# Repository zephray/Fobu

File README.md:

Fobu
====

Fobu is a key fob sized open-source FPGA + ARM handheld device (formerly VerilogBoy Handheld). The intended usages are portable FPGA retro gaming system (FPGA-based implementation, ARM-based emulation, or both) and portable audio (both general format such as mp3, FLAC, etc. via ARM core and retro VGM such as FM, SSG, etc. via FPGA implementation) player. However, the architecture should allow other usages as well.

# Hardware

## Block Diagram

## Photos

The photo of an Fobu r0.2 prototype:

# Software

The following third-party middlewares are used in the project:

 * Amazon FreeRTOS Operating System (MIT)
 * id3v2lib by Lorenzo Ruiz (BSD 2-Clause)
 * minimp3 by lieff (Public Domain)
 * FatFs by ChaN (See source file)
 * tjpgd by ChaN (See source file)

# License

If not otherwise specified, all the materials provided in this repository are licensed under MIT license.

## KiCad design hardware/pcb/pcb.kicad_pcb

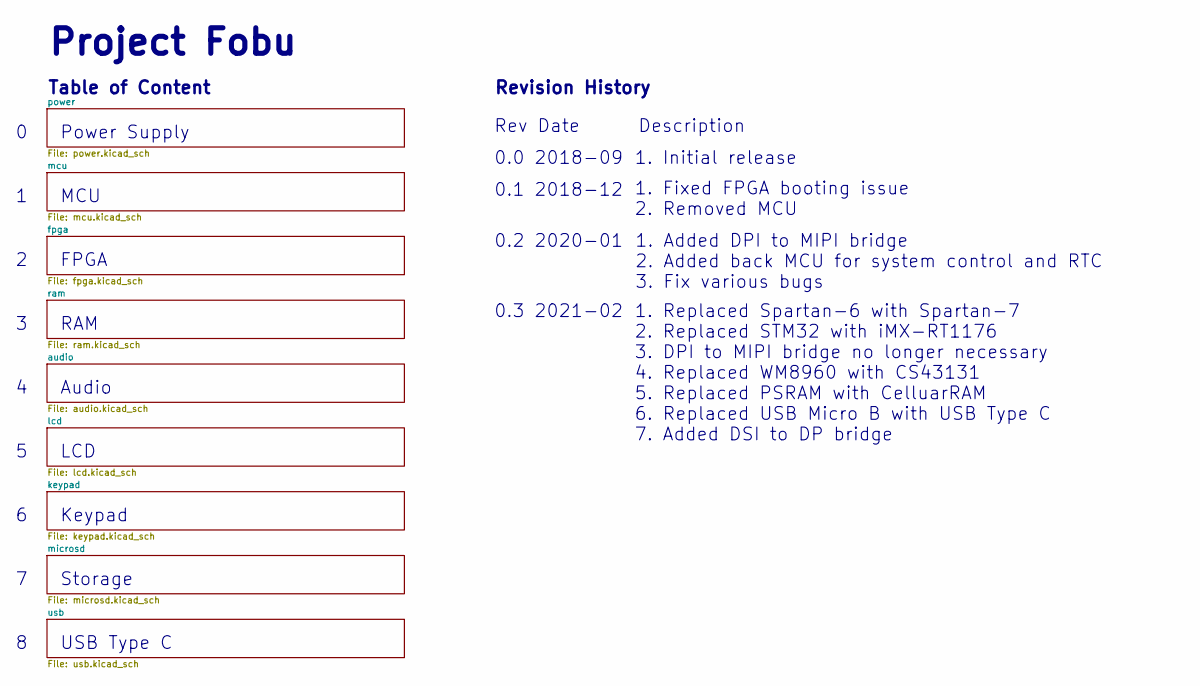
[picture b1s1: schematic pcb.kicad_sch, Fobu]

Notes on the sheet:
Project Fobu
Table of Content
Power Supply
MCU
FPGA
RAM
Audio
LCD
Keypad
Storage
USB Type C
Revision History
Rev Date Description
0.0 2018-09
0.1 2018-12
0.2 2020-01
0.3 2021-02
1. Initial release
1. Fixed FPGA booting issue 2. Removed MCU
1. Replaced Spartan-6 with Spartan-7 2. Replaced STM32 with iMX-RT1176 3. DPI to MIPI bridge no longer necessary 4. Replaced WM8960 with CS43131 5. Replaced PSRAM with CelluarRAM 6. Replaced USB Micro B with USB Type C 7. Added DSI to DP bridge
1. Added DPI to MIPI bridge 2. Added back MCU for system control and RTC 3. Fix various bugs

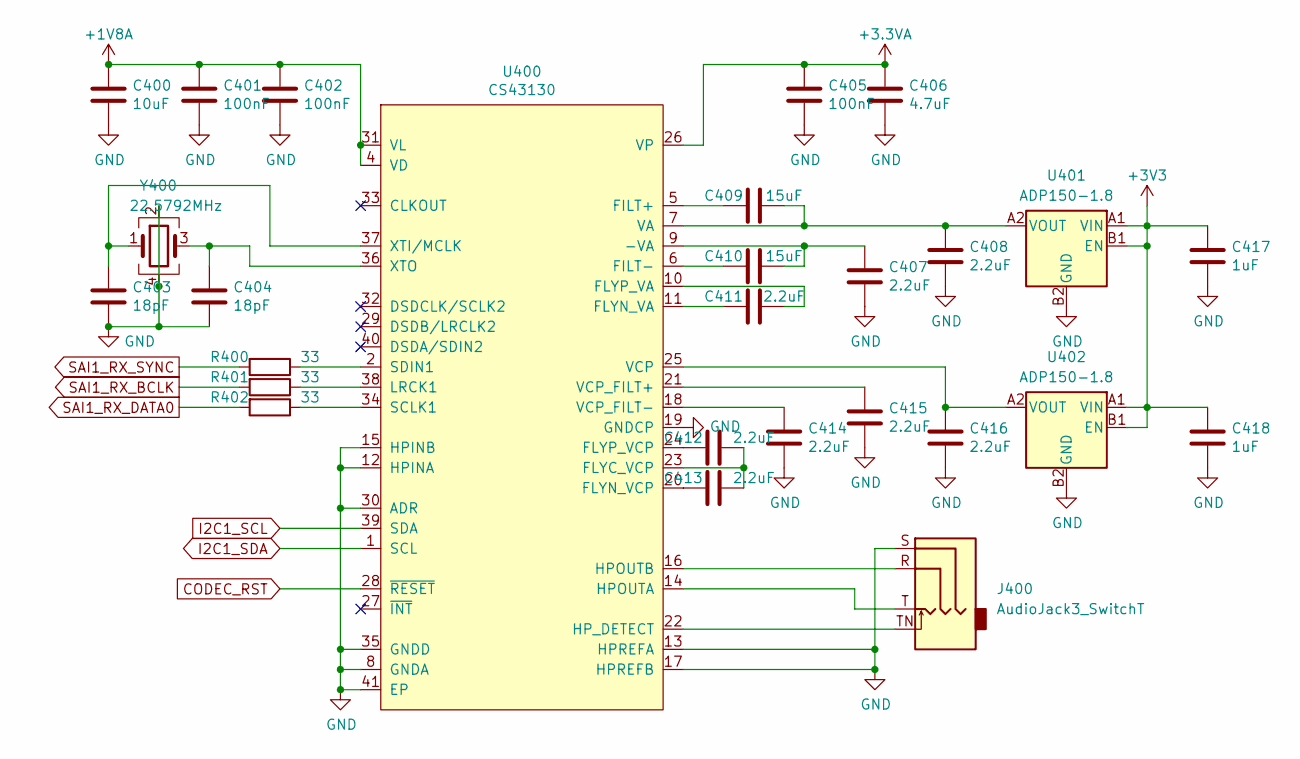
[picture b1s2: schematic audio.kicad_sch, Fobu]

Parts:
C400: 10uF; C_0402_1005Metric
C401, C402, C405: 100nF; C_0201_0603Metric
C403, C404: 18pF; C_0201_0603Metric
C406: 4.7uF; C_0402_1005Metric
C407, C408, C411, C412, C413, C414, C415, C416: 2.2uF; C_0402_1005Metric
C409, C410: 15uF; C_0603_1608Metric
C417, C418: 1uF; C_0402_1005Metric
J400: AudioJack3_SwitchT; PJ-327E
R400, R401, R402: 33; R_0402_1005Metric
U400: CS43130; QFN-40-1EP_5x5mm_P0.4mm_EP3.6x3.6mm_ThermalVias
U401, U402: ADP150-1.8; CSP-4_2x2_0.8x0.8mm
Y400: 22.5792MHz; Oscillator_SMD_Abracon_ASE-4Pin_3.2x2.5mm

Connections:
+1V8A: C400.1, C401.1, C402.1, U400.4 (VD), U400.31 (VL); also elsewhere on the board
+3.3VA: C405.1, C406.1, U400.26 (VP); also elsewhere on the board
+3V3: C417.1, C418.1, U401.A1 (VIN), U401.B1 (EN), U402.A1 (VIN), U402.B1 (EN); also elsewhere on the board
CODEC_RST: U400.28 (~RESET)
GND: C400.2, C401.2, C402.2, C403.2, C404.2, C405.2, C406.2, C407.2, C408.2, C414.2, C415.2, C416.2, C417.2, C418.2, J400.S, U400.8 (GNDA), U400.12 (HPINA), U400.13 (HPREFA), U400.15 (HPINB), U400.17 (HPREFB), U400.19 (GNDCP), U400.30 (ADR), U400.35 (GNDD), U400.41 (EP), U401.B2 (GND), U402.B2 (GND), Y400.2, Y400.4; also elsewhere on the board
I2C1_SCL: U400.39 (SDA); also elsewhere on the board
I2C1_SDA: U400.1 (SCL); also elsewhere on the board
unnamed: C403.1, U400.37 (XTI/MCLK), Y400.1
unnamed: C404.1, U400.36 (XTO), Y400.3
unnamed: C407.1, C410.1, U400.9 (-VA)
unnamed: C408.1, C409.1, U400.7 (VA), U401.A2 (VOUT)
unnamed: C409.2, U400.5 (FILT+)
unnamed: C410.2, U400.6 (FILT-)
unnamed: C411.1, U400.10 (FLYP_VA)
unnamed: C411.2, U400.11 (FLYN_VA)
unnamed: C412.1, C413.1, U400.23 (FLYC_VCP)
unnamed: C412.2, U400.24 (FLYP_VCP)
unnamed: C413.2, U400.20 (FLYN_VCP)
unnamed: C414.1, U400.18 (VCP_FILT-)
unnamed: C415.1, U400.21 (VCP_FILT+)
unnamed: C416.1, U400.25 (VCP), U402.A2 (VOUT)
unnamed: J400.R, U400.16 (HPOUTB)
unnamed: J400.T, U400.14 (HPOUTA)
unnamed: J400.TN, U400.22 (HP_DETECT)
unnamed: R400.1, U400.2 (SDIN1)
unnamed: R401.1, U400.38 (LRCK1)
unnamed: R402.1, U400.34 (SCLK1)
SAI1_RX_BCLK: R401.2; also elsewhere on the board
SAI1_RX_DATA0: R402.2; also elsewhere on the board
SAI1_RX_SYNC: R400.2; also elsewhere on the board

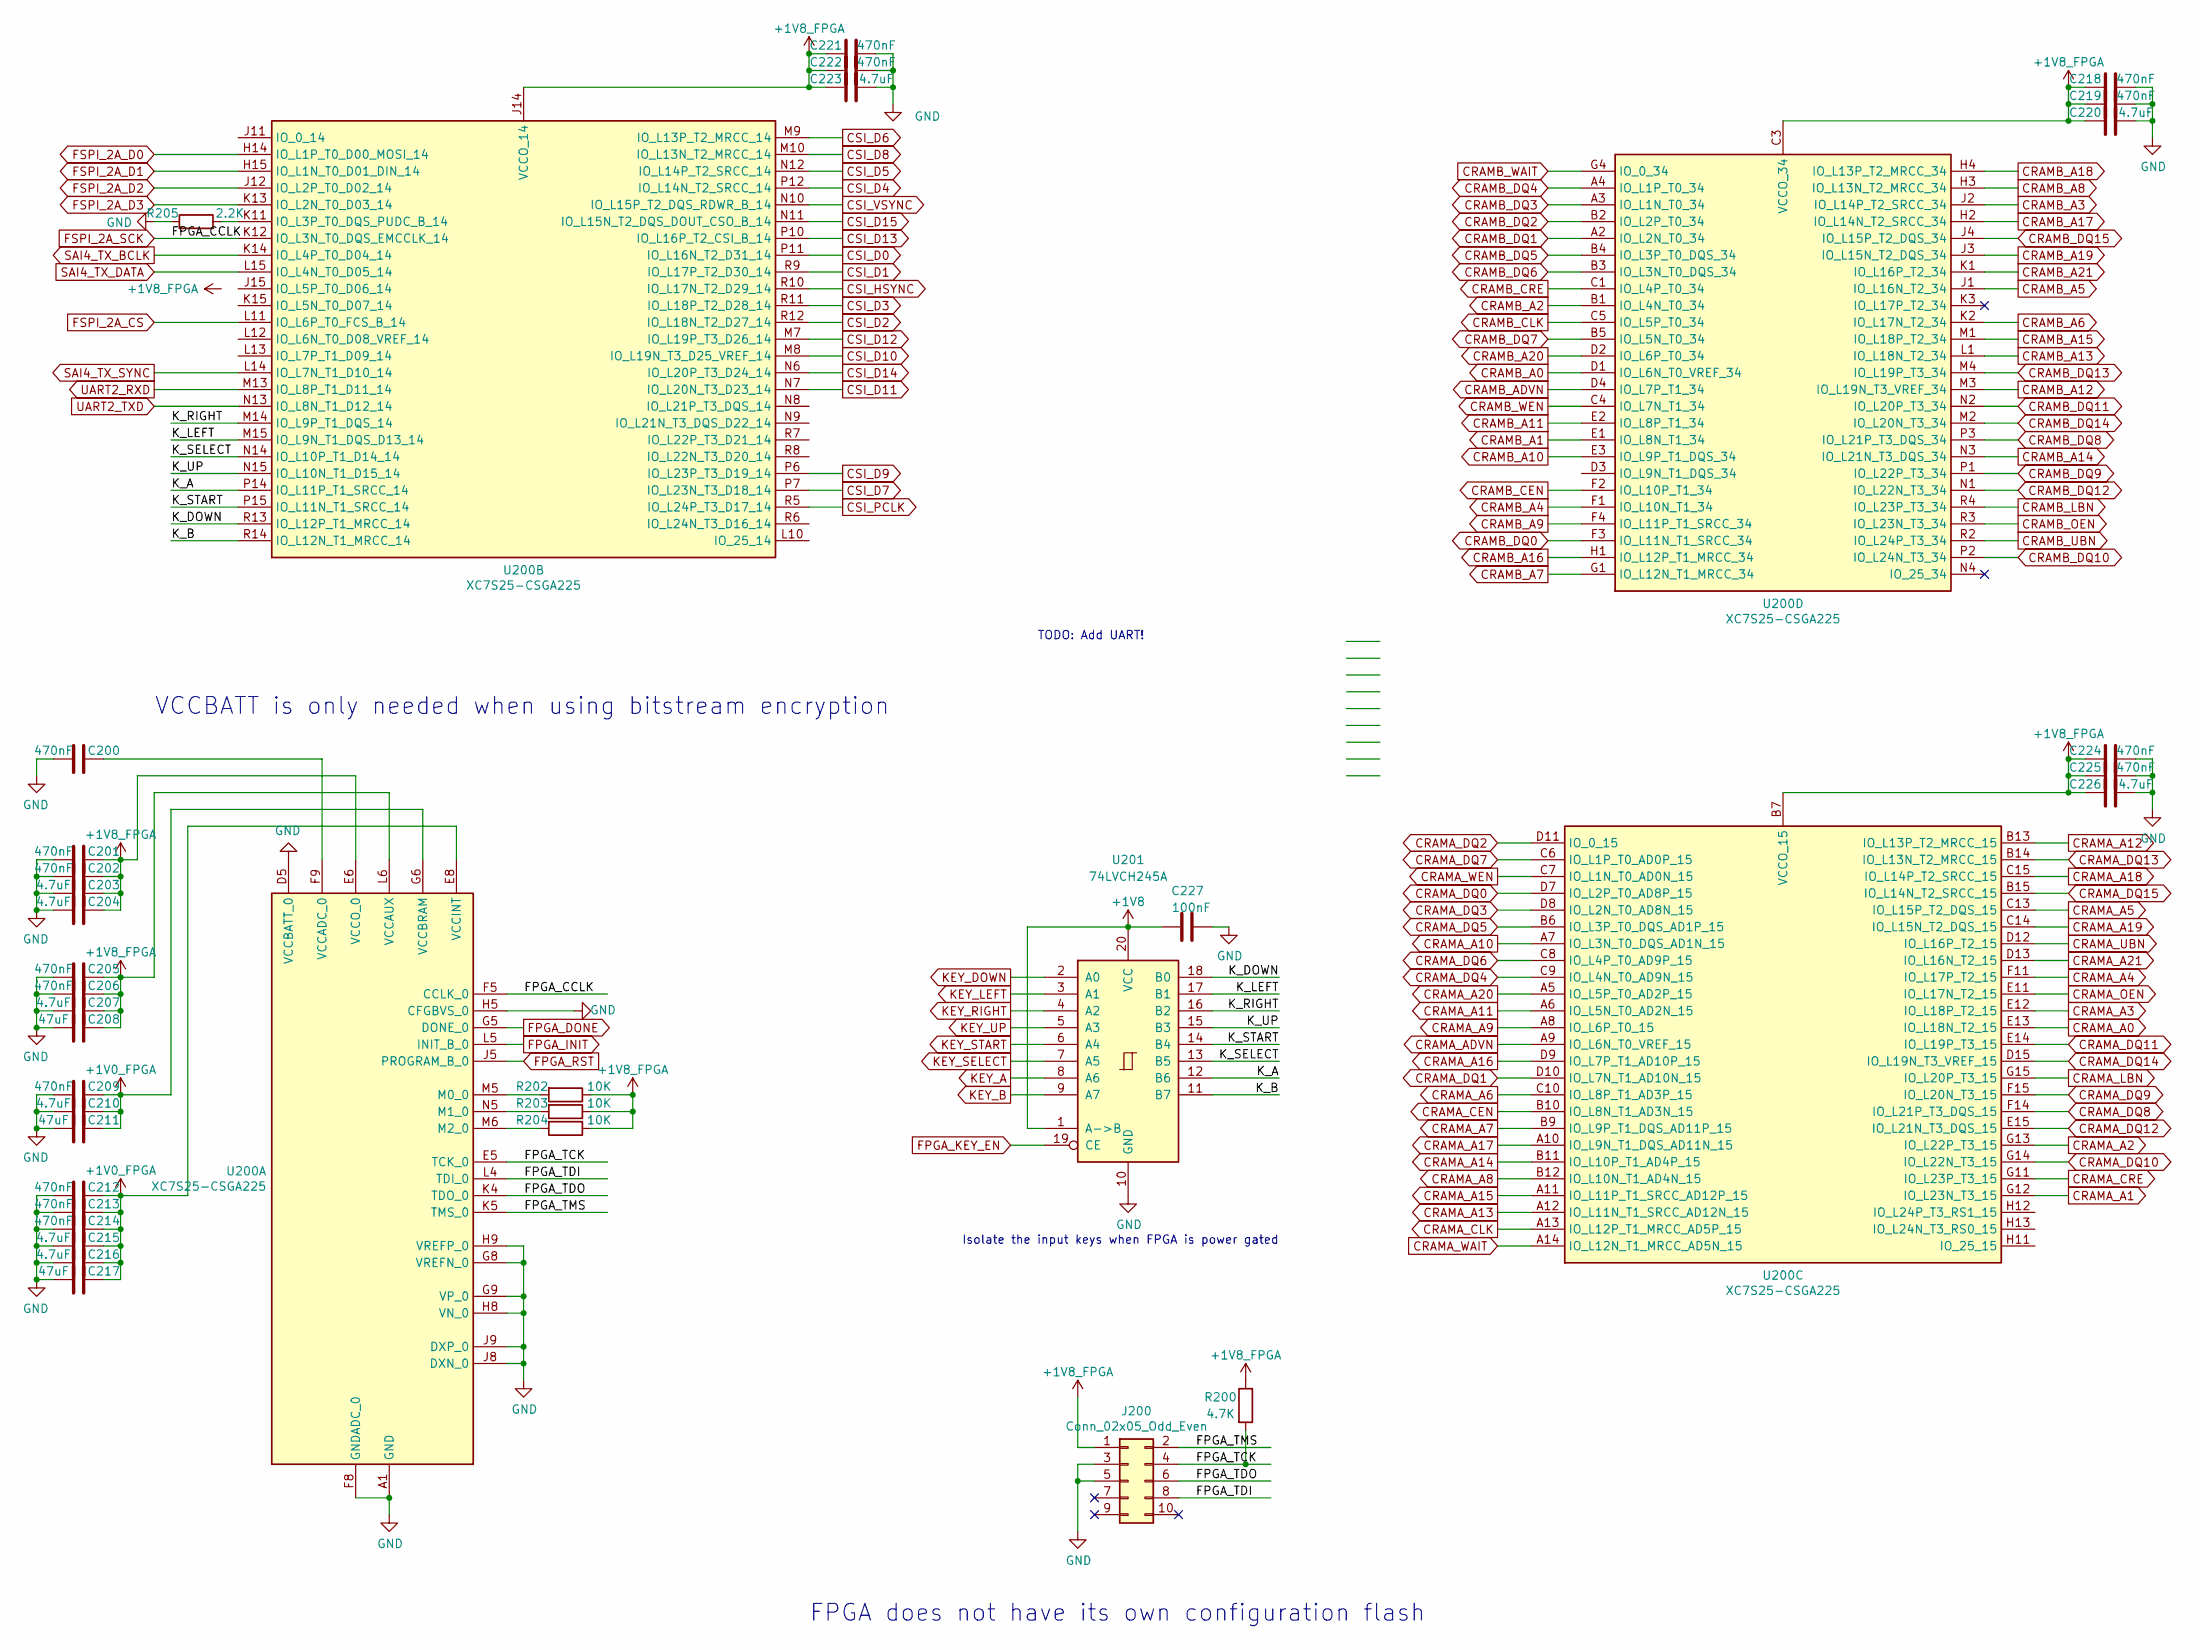
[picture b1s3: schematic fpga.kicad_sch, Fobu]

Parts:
C200, C201, C202, C205, C206, C209, C212, C213, C214, C218, C219, C221, C222, C224, C225: 470nF; C_0201_0603Metric
C203, C204, C207, C210, C215, C216, C220, C223, C226: 4.7uF; C_0402_1005Metric
C208, C211, C217: 47uF; C_0603_1608Metric
C227: 100nF; C_0201_0603Metric
J200: Conn_02x05_Odd_Even; PinHeader_2x05_P1.27mm_Vertical_SMD
R200: 4.7K; R_0402_1005Metric
R202, R203, R204: 10K; R_0402_1005Metric
R205: 2.2K; R_0402_1005Metric
U200: XC7S25-CSGA225; Xilinx_CSGA225
U201: 74LVCH245A; DHVQFN-20_EP_4.5x2.5_Pitch0.5mm

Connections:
+1V0_FPGA: C209.2, C210.2, C211.2, C212.2, C213.2, C214.2, C215.2, C216.2, C217.2, U200.E8 (VCCINT), U200.E10 (VCCINT), U200.F7 (VCCINT), U200.G6 (VCCBRAM), U200.G10 (VCCINT), U200.H7 (VCCINT), U200.J6 (VCCBRAM), U200.J10 (VCCINT), U200.K7 (VCCINT), U200.K9 (VCCINT); also elsewhere on the board
+1V8: C227.1, U201.1 (A->B), U201.20 (VCC); also elsewhere on the board
/fpga/FPGA_TCK: J200.4, R200.2, U200.E5 (TCK_0)
/fpga/FPGA_TDI: J200.8, U200.L4 (TDI_0)
/fpga/FPGA_TDO: J200.6, U200.K4 (TDO_0)
/fpga/FPGA_TMS: J200.2, U200.K5 (TMS_0)
/fpga/K_A: U200.P14 (IO_L11P_T1_SRCC_14), U201.12 (B6)
/fpga/K_B: U200.R14 (IO_L12N_T1_MRCC_14), U201.11 (B7)
/fpga/K_DOWN: U200.R13 (IO_L12P_T1_MRCC_14), U201.18 (B0)
/fpga/K_LEFT: U200.M15 (IO_L9N_T1_DQS_D13_14), U201.17 (B1)
/fpga/K_RIGHT: U200.M14 (IO_L9P_T1_DQS_14), U201.16 (B2)
/fpga/K_SELECT: U200.N14 (IO_L10P_T1_D14_14), U201.13 (B5)
/fpga/K_START: U200.P15 (IO_L11N_T1_SRCC_14), U201.14 (B4)
/fpga/K_UP: U200.N15 (IO_L10N_T1_D15_14), U201.15 (B3)
CRAMA_A0: U200.E13 (IO_L18N_T2_15); also elsewhere on the board
CRAMA_A1: U200.G12 (IO_L23N_T3_15); also elsewhere on the board
CRAMA_A2: U200.G13 (IO_L22P_T3_15); also elsewhere on the board
CRAMA_A3: U200.E12 (IO_L18P_T2_15); also elsewhere on the board
CRAMA_A4: U200.F11 (IO_L17P_T2_15); also elsewhere on the board
CRAMA_A5: U200.C13 (IO_L15P_T2_DQS_15); also elsewhere on the board
CRAMA_A6: U200.C10 (IO_L8P_T1_AD3P_15); also elsewhere on the board
CRAMA_A7: U200.B9 (IO_L9P_T1_DQS_AD11P_15); also elsewhere on the board
CRAMA_A8: U200.B12 (IO_L10N_T1_AD4N_15); also elsewhere on the board
CRAMA_A9: U200.A8 (IO_L6P_T0_15); also elsewhere on the board
CRAMA_A10: U200.A7 (IO_L3N_T0_DQS_AD1N_15); also elsewhere on the board
CRAMA_A11: U200.A6 (IO_L5N_T0_AD2N_15); also elsewhere on the board
CRAMA_A12: U200.B13 (IO_L13P_T2_MRCC_15); also elsewhere on the board
CRAMA_A13: U200.A12 (IO_L11N_T1_SRCC_AD12N_15); also elsewhere on the board
CRAMA_A14: U200.B11 (IO_L10P_T1_AD4P_15); also elsewhere on the board
CRAMA_A15: U200.A11 (IO_L11P_T1_SRCC_AD12P_15); also elsewhere on the board
CRAMA_A16: U200.D9 (IO_L7P_T1_AD10P_15); also elsewhere on the board
CRAMA_A17: U200.A10 (IO_L9N_T1_DQS_AD11N_15); also elsewhere on the board
CRAMA_A18: U200.C15 (IO_L14P_T2_SRCC_15); also elsewhere on the board
CRAMA_A19: U200.C14 (IO_L15N_T2_DQS_15); also elsewhere on the board
CRAMA_A20: U200.A5 (IO_L5P_T0_AD2P_15); also elsewhere on the board
CRAMA_A21: U200.D13 (IO_L16N_T2_15); also elsewhere on the board
CRAMA_ADVN: U200.A9 (IO_L6N_T0_VREF_15); also elsewhere on the board
CRAMA_CEN: U200.B10 (IO_L8N_T1_AD3N_15); also elsewhere on the board
CRAMA_CLK: U200.A13 (IO_L12P_T1_MRCC_AD5P_15); also elsewhere on the board
CRAMA_CRE: U200.G11 (IO_L23P_T3_15); also elsewhere on the board
CRAMA_DQ0: U200.D7 (IO_L2P_T0_AD8P_15); also elsewhere on the board
CRAMA_DQ1: U200.D10 (IO_L7N_T1_AD10N_15); also elsewhere on the board
CRAMA_DQ2: U200.D11 (IO_0_15); also elsewhere on the board
CRAMA_DQ3: U200.D8 (IO_L2N_T0_AD8N_15); also elsewhere on the board
CRAMA_DQ4: U200.C9 (IO_L4N_T0_AD9N_15); also elsewhere on the board
CRAMA_DQ5: U200.B6 (IO_L3P_T0_DQS_AD1P_15); also elsewhere on the board
CRAMA_DQ6: U200.C8 (IO_L4P_T0_AD9P_15); also elsewhere on the board
CRAMA_DQ7: U200.C6 (IO_L1P_T0_AD0P_15); also elsewhere on the board
CRAMA_DQ8: U200.F14 (IO_L21P_T3_DQS_15); also elsewhere on the board
CRAMA_DQ9: U200.F15 (IO_L20N_T3_15); also elsewhere on the board
CRAMA_DQ10: U200.G14 (IO_L22N_T3_15); also elsewhere on the board
CRAMA_DQ11: U200.E14 (IO_L19P_T3_15); also elsewhere on the board
CRAMA_DQ12: U200.E15 (IO_L21N_T3_DQS_15); also elsewhere on the board
CRAMA_DQ13: U200.B14 (IO_L13N_T2_MRCC_15); also elsewhere on the board
CRAMA_DQ14: U200.D15 (IO_L19N_T3_VREF_15); also elsewhere on the board
CRAMA_DQ15: U200.B15 (IO_L14N_T2_SRCC_15); also elsewhere on the board
CRAMA_LBN: U200.G15 (IO_L20P_T3_15); also elsewhere on the board
CRAMA_OEN: U200.E11 (IO_L17N_T2_15); also elsewhere on the board
CRAMA_UBN: U200.D12 (IO_L16P_T2_15); also elsewhere on the board
CRAMA_WAIT: U200.A14 (IO_L12N_T1_MRCC_AD5N_15); also elsewhere on the board
CRAMA_WEN: U200.C7 (IO_L1N_T0_AD0N_15); also elsewhere on the board
CRAMB_A0: U200.D1 (IO_L6N_T0_VREF_34); also elsewhere on the board
CRAMB_A1: U200.E1 (IO_L8N_T1_34); also elsewhere on the board
CRAMB_A2: U200.B1 (IO_L4N_T0_34); also elsewhere on the board
CRAMB_A3: U200.J2 (IO_L14P_T2_SRCC_34); also elsewhere on the board
CRAMB_A4: U200.F1 (IO_L10N_T1_34); also elsewhere on the board
CRAMB_A5: U200.J1 (IO_L16N_T2_34); also elsewhere on the board
CRAMB_A6: U200.K2 (IO_L17N_T2_34); also elsewhere on the board
CRAMB_A7: U200.G1 (IO_L12N_T1_MRCC_34); also elsewhere on the board
CRAMB_A8: U200.H3 (IO_L13N_T2_MRCC_34); also elsewhere on the board
CRAMB_A9: U200.F4 (IO_L11P_T1_SRCC_34); also elsewhere on the board
CRAMB_A10: U200.E3 (IO_L9P_T1_DQS_34); also elsewhere on the board
CRAMB_A11: U200.E2 (IO_L8P_T1_34); also elsewhere on the board
CRAMB_A12: U200.M3 (IO_L19N_T3_VREF_34); also elsewhere on the board
CRAMB_A13: U200.L1 (IO_L18N_T2_34); also elsewhere on the board
CRAMB_A14: U200.N3 (IO_L21N_T3_DQS_34); also elsewhere on the board
CRAMB_A15: U200.M1 (IO_L18P_T2_34); also elsewhere on the board
CRAMB_A16: U200.H1 (IO_L12P_T1_MRCC_34); also elsewhere on the board
CRAMB_A17: U200.H2 (IO_L14N_T2_SRCC_34); also elsewhere on the board
CRAMB_A18: U200.H4 (IO_L13P_T2_MRCC_34); also elsewhere on the board
CRAMB_A19: U200.J3 (IO_L15N_T2_DQS_34); also elsewhere on the board
CRAMB_A20: U200.D2 (IO_L6P_T0_34); also elsewhere on the board
CRAMB_A21: U200.K1 (IO_L16P_T2_34); also elsewhere on the board
CRAMB_ADVN: U200.D4 (IO_L7P_T1_34); also elsewhere on the board
CRAMB_CEN: U200.F2 (IO_L10P_T1_34); also elsewhere on the board
CRAMB_CLK: U200.C5 (IO_L5P_T0_34); also elsewhere on the board
CRAMB_CRE: U200.C1 (IO_L4P_T0_34); also elsewhere on the board
CRAMB_DQ0: U200.F3 (IO_L11N_T1_SRCC_34); also elsewhere on the board
CRAMB_DQ1: U200.A2 (IO_L2N_T0_34); also elsewhere on the board
CRAMB_DQ2: U200.B2 (IO_L2P_T0_34); also elsewhere on the board
CRAMB_DQ3: U200.A3 (IO_L1N_T0_34); also elsewhere on the board
CRAMB_DQ4: U200.A4 (IO_L1P_T0_34); also elsewhere on the board
CRAMB_DQ5: U200.B4 (IO_L3P_T0_DQS_34); also elsewhere on the board
CRAMB_DQ6: U200.B3 (IO_L3N_T0_DQS_34); also elsewhere on the board
CRAMB_DQ7: U200.B5 (IO_L5N_T0_34); also elsewhere on the board
CRAMB_DQ8: U200.P3 (IO_L21P_T3_DQS_34); also elsewhere on the board
CRAMB_DQ9: U200.P1 (IO_L22P_T3_34); also elsewhere on the board
CRAMB_DQ10: U200.P2 (IO_L24N_T3_34); also elsewhere on the board
CRAMB_DQ11: U200.N2 (IO_L20P_T3_34); also elsewhere on the board
CRAMB_DQ12: U200.N1 (IO_L22N_T3_34); also elsewhere on the board
CRAMB_DQ13: U200.M4 (IO_L19P_T3_34); also elsewhere on the board
CRAMB_DQ14: U200.M2 (IO_L20N_T3_34); also elsewhere on the board
CRAMB_DQ15: U200.J4 (IO_L15P_T2_DQS_34); also elsewhere on the board
CRAMB_LBN: U200.R4 (IO_L23P_T3_34); also elsewhere on the board
CRAMB_OEN: U200.R3 (IO_L23N_T3_34); also elsewhere on the board
CRAMB_UBN: U200.R2 (IO_L24P_T3_34); also elsewhere on the board
CRAMB_WAIT: U200.G4 (IO_0_34); also elsewhere on the board
CRAMB_WEN: U200.C4 (IO_L7N_T1_34); also elsewhere on the board
CSI_D0: U200.P11 (IO_L16N_T2_D31_14); also elsewhere on the board
CSI_D1: U200.R9 (IO_L17P_T2_D30_14); also elsewhere on the board
CSI_D2: U200.R12 (IO_L18N_T2_D27_14); also elsewhere on the board
CSI_D3: U200.R11 (IO_L18P_T2_D28_14); also elsewhere on the board
CSI_D4: U200.P12 (IO_L14N_T2_SRCC_14); also elsewhere on the board
CSI_D5: U200.N12 (IO_L14P_T2_SRCC_14); also elsewhere on the board
CSI_D6: U200.M9 (IO_L13P_T2_MRCC_14); also elsewhere on the board
CSI_D7: U200.P7 (IO_L23N_T3_D18_14); also elsewhere on the board
CSI_D8: U200.M10 (IO_L13N_T2_MRCC_14); also elsewhere on the board
CSI_D9: U200.P6 (IO_L23P_T3_D19_14); also elsewhere on the board
CSI_D10: U200.M8 (IO_L19N_T3_D25_VREF_14); also elsewhere on the board
CSI_D11: U200.N7 (IO_L20N_T3_D23_14); also elsewhere on the board
CSI_D12: U200.M7 (IO_L19P_T3_D26_14); also elsewhere on the board
CSI_D13: U200.P10 (IO_L16P_T2_CSI_B_14); also elsewhere on the board
CSI_D14: U200.N6 (IO_L20P_T3_D24_14); also elsewhere on the board
CSI_D15: U200.N11 (IO_L15N_T2_DQS_DOUT_CSO_B_14); also elsewhere on the board
CSI_HSYNC: U200.R10 (IO_L17N_T2_D29_14); also elsewhere on the board
CSI_PCLK: U200.R5 (IO_L24P_T3_D17_14); also elsewhere on the board
CSI_VSYNC: U200.N10 (IO_L15P_T2_DQS_RDWR_B_14); also elsewhere on the board
FPGA_DONE: U200.G5 (DONE_0); also elsewhere on the board
FPGA_INIT: U200.L5 (INIT_B_0); also elsewhere on the board
FPGA_KEY_EN: U201.19 (CE); also elsewhere on the board
FPGA_RST: U200.J5 (PROGRAM_B_0); also elsewhere on the board
FSPI_2A_CS: U200.L11 (IO_L6P_T0_FCS_B_14); also elsewhere on the board
FSPI_2A_D0: U200.H14 (IO_L1P_T0_D00_MOSI_14); also elsewhere on the board
FSPI_2A_D1: U200.H15 (IO_L1N_T0_D01_DIN_14); also elsewhere on the board
FSPI_2A_D2: U200.J12 (IO_L2P_T0_D02_14); also elsewhere on the board
FSPI_2A_D3: U200.K13 (IO_L2N_T0_D03_14); also elsewhere on the board
FSPI_2A_SCK: U200.F5 (CCLK_0), U200.K12 (IO_L3N_T0_DQS_EMCCLK_14); also elsewhere on the board
GND: C200.1, C201.1, C202.1, C203.1, C204.1, C205.1, C206.1, C207.1, C208.1, C209.1, C210.1, C211.1, C212.1, C213.1, C214.1, C215.1, C216.1, C217.1, C218.1, C219.1, C220.1, C221.1, C222.1, C223.1, C224.1, C225.1, C226.1, C227.2, J200.3, J200.5, R205.1, U200.A1 (GND), U200.A15 (GND), U200.B8 (GND), U200.C2 (GND), U200.C12 (GND), U200.D5 (VCCBATT_0), U200.D6 (GND), U200.D14 (GND), U200.E4 (GND), U200.E7 (GND), U200.E9 (GND), U200.F6 (GND), U200.F8 (GNDADC_0), U200.F10 (GND), U200.F13 (GND), U200.G3 (GND), U200.G7 (GND), U200.G8 (VREFN_0), U200.G9 (VP_0), U200.H5 (CFGBVS_0), U200.H6 (GND), U200.H8 (VN_0), U200.H9 (VREFP_0), U200.H10 (GND), U200.J7 (GND), U200.J8 (DXN_0), U200.J9 (DXP_0), U200.J13 (GND), U200.K6 (GND), U200.K8 (GND), U200.K10 (GND), U200.L2 (GND), U200.L7 (GND), U200.L9 (GND), U200.M11 (GND), U200.P4 (GND), U200.P8 (GND), U200.P13 (GND), U200.R1 (GND), U200.R15 (GND), U201.10 (GND); also elsewhere on the board
KEY_A: U201.8 (A6); also elsewhere on the board
KEY_B: U201.9 (A7); also elsewhere on the board
KEY_DOWN: U201.2 (A0); also elsewhere on the board
KEY_LEFT: U201.3 (A1); also elsewhere on the board
KEY_RIGHT: U201.4 (A2); also elsewhere on the board
KEY_SELECT: U201.7 (A5); also elsewhere on the board
KEY_START: U201.6 (A4); also elsewhere on the board
KEY_UP: U201.5 (A3); also elsewhere on the board
unnamed: R202.2, U200.M5 (M0_0)
unnamed: R203.2, U200.N5 (M1_0)
unnamed: R204.2, U200.M6 (M2_0)
unnamed: R205.2, U200.K11 (IO_L3P_T0_DQS_PUDC_B_14)
SAI4_TX_BCLK: U200.K14 (IO_L4P_T0_D04_14); also elsewhere on the board
SAI4_TX_DATA: U200.L15 (IO_L4N_T0_D05_14); also elsewhere on the board
SAI4_TX_SYNC: U200.L14 (IO_L7N_T1_D10_14); also elsewhere on the board
UART2_RXD: U200.M13 (IO_L8P_T1_D11_14); also elsewhere on the board
UART2_TXD: U200.N13 (IO_L8N_T1_D12_14); also elsewhere on the board

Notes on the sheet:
VCCBATT is only needed when using bitstream encryption
FPGA does not have its own configuration flash
TODO: Add UART!
Isolate the input keys when FPGA is power gated

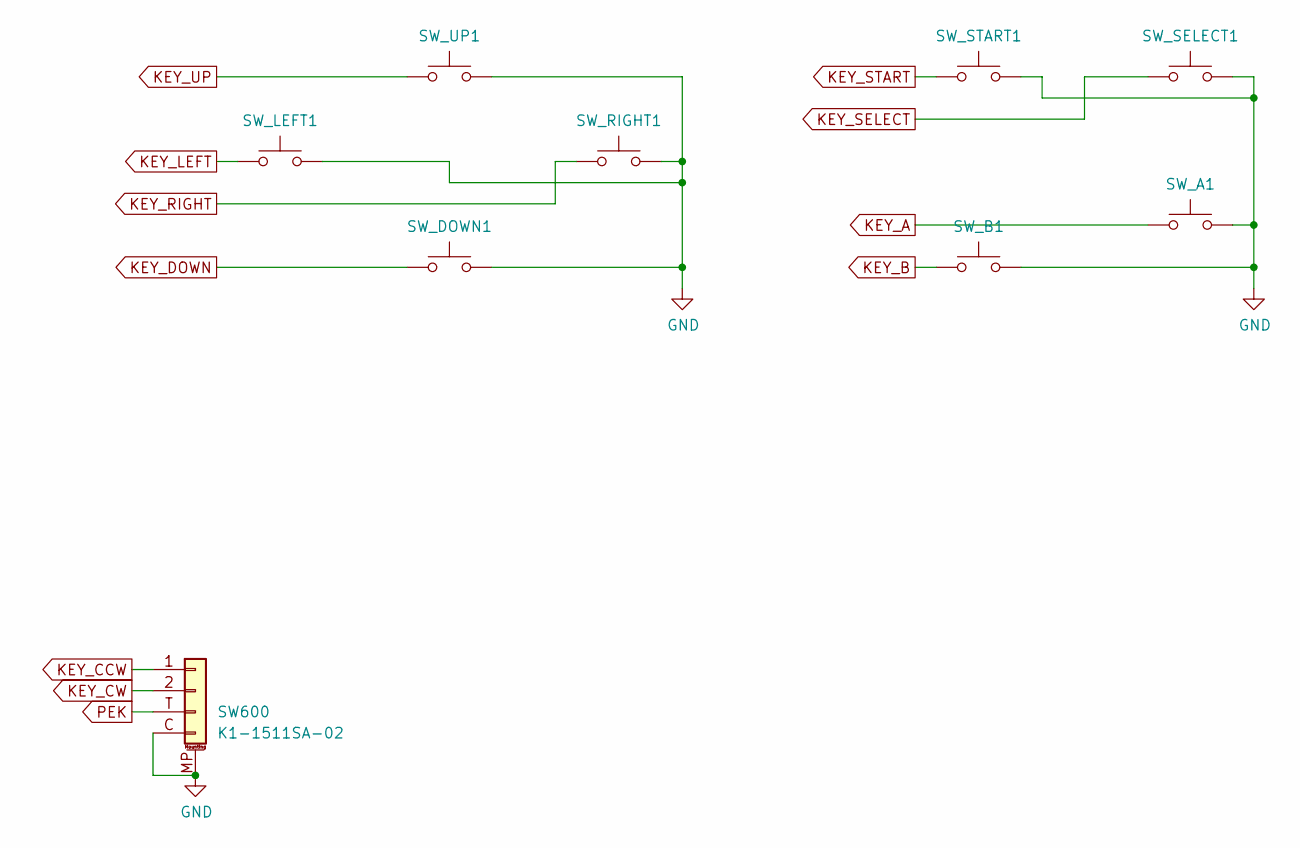
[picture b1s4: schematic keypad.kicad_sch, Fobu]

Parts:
SW600: K1-1511SA-02
SW_A1: SW_Push; SW_SPST_K21177SR
SW_B1: SW_Push; SW_SPST_K21177SR
SW_DOWN1: SW_Push; SW_SPST_K21177SR
SW_LEFT1: SW_Push; SW_SPST_K21177SR
SW_RIGHT1: SW_Push; SW_SPST_K21177SR
SW_SELECT1: SW_Push; SW_SPST_K21177SR
SW_START1: SW_Push; SW_SPST_K21177SR
SW_UP1: SW_Push; SW_SPST_K21177SR

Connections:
GND: SW600.C (Pin_4), SW600.MP (MountPin), SW_A1.2, SW_B1.2, SW_DOWN1.2, SW_LEFT1.2, SW_RIGHT1.2, SW_SELECT1.2, SW_START1.2, SW_UP1.2; also elsewhere on the board
KEY_A: SW_A1.1; also elsewhere on the board
KEY_B: SW_B1.1; also elsewhere on the board
KEY_CCW: SW600.1
KEY_CW: SW600.2
KEY_DOWN: SW_DOWN1.1; also elsewhere on the board
KEY_LEFT: SW_LEFT1.1; also elsewhere on the board
KEY_RIGHT: SW_RIGHT1.1; also elsewhere on the board
KEY_SELECT: SW_SELECT1.1; also elsewhere on the board
KEY_START: SW_START1.1; also elsewhere on the board
KEY_UP: SW_UP1.1; also elsewhere on the board
PEK: SW600.T (Pin_3); also elsewhere on the board

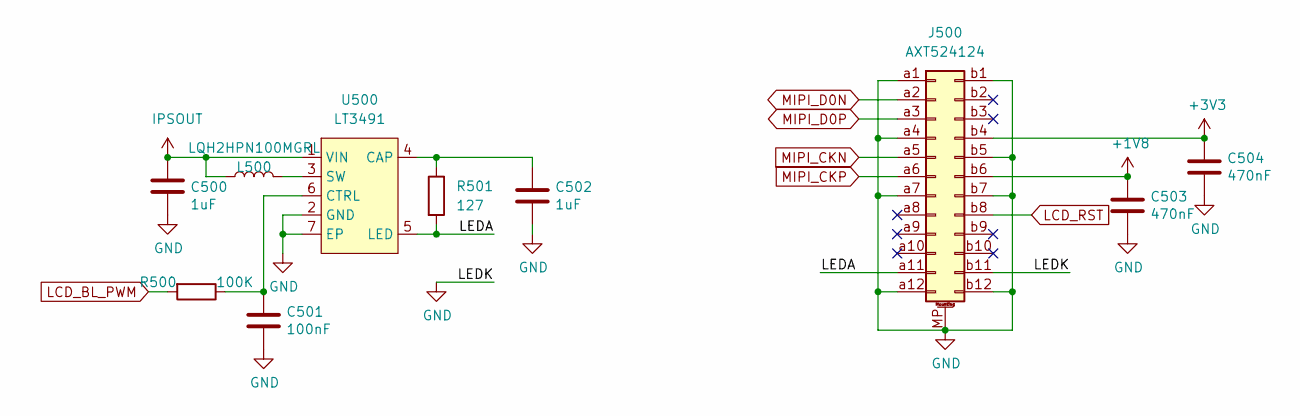
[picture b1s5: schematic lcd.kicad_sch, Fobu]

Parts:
C500, C502: 1uF; C_0402_1005Metric
C501: 100nF; C_0201_0603Metric
C503, C504: 470nF; C_0201_0603Metric
J500: AXT524124
L500: LQH2HPN100MGRL; L_1008_2520Metric
R500: 100K; R_0402_1005Metric
R501: 127; R_0402_1005Metric
U500: LT3491; DFN-6-1EP_2x2mm_P0.5mm_EP0.61x1.42mm

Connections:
+1V8: C503.1, J500.b6; also elsewhere on the board
+3V3: C504.1, J500.b4; also elsewhere on the board
/lcd/LEDA: J500.a11, R501.2, U500.5 (LED)
GND: C500.2, C501.2, C502.2, C503.2, C504.2, J500.MP (MountPin), J500.a1, J500.a4, J500.a7, J500.a12, J500.b1, J500.b5, J500.b7, J500.b11, J500.b12, U500.2 (GND), U500.7 (EP); also elsewhere on the board
IPSOUT: C500.1, L500.1, U500.1 (VIN); also elsewhere on the board
LCD_BL_PWM: R500.2
LCD_RST: J500.b8
MIPI_CKN: J500.a5; also elsewhere on the board
MIPI_CKP: J500.a6; also elsewhere on the board
MIPI_D0N: J500.a2; also elsewhere on the board
MIPI_D0P: J500.a3; also elsewhere on the board
unnamed: C501.1, R500.1, U500.6 (CTRL)
unnamed: C502.1, R501.1, U500.4 (CAP)
unnamed: L500.2, U500.3 (SW)
